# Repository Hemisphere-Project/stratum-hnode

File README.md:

# STRATUM
NodeJS Server / esp8266+W5500 Node

You can find a basic usage in demo.js

### Install
`npm install --save hemisphere-project/stratum-hnode`

### Basic usage
```js
var hnode = require('hnode')();   // load and instanciate the library
var server = new hnode.Server();  // instantiate a server
server.start();                   // start the server
```

### Options
```js
var hnode = require('hnode')({
  // This are the default options
  PORT_SERVER: 3737,            // Working UDP port
  TIME_TICK: 100,               // Watchdog timer ms
  TIME_OFFLINE: 1000,           // Offline Time
  TIME_GONE: 3000,              // Gone Time
  NLEDS_STRIPS: 90,             // N leds per strips
  NSTRIPS_CLIENT: 4,            // N strips per client
  log : msg => console.log(msg) // custom log function (to write in file, etc)
});
var server = new hnode.Server()
server.start()
```

### API
#### Server methods:
  `.getNodeByIP( ip )`      
      return a Node or undefined

  `.getNodeByName( name )`  
       return a Node or undefined

  `.getAllNodes()`  
      return an array with all known Nodes

  `.setAll( rgb )`  
      apply one color (rgb array) to every leds, rgb = [r,g,b]

  `.blackout()`  
      switch off every leds

#### Server events:
  `.on('newnode', function(node){ ... })`   
       triggered when a new Node is discovered

  `.on('tick', function(node){ ... })`
       server ticker, can be use as main sequencer

#### Node methods:
  `.setLed( strip, led, rgb )`   
       apply rgb array to a specific led, rgb = [r, g, b]
       array[3]

  `.setStrip( led, rgbs )`   
       apply rgbs array of array to a strip, rgbs = [ [r, g, b],  [r, g, b], ... ]
       array[NUM_LEDS_PER_STRIP][3]

  `.setAll( rgbs )`   
       apply a whole set of 4 strips, rgbs = [ [ [r, g, b],  [r, g, b], ... ], ... ]
       array[NSTRIPS_PER_CLIENTS][NUM_LEDS_PER_STRIP][3]

  `.randomize()`   
       randomize all values of the node's leds

#### Node attributes (read-only):
  `.name`   
  `.ip`

#### Node events:
  `.on('start', function(node){ ... }) `  
       triggered when a node is started

  `.on('online', function(node){ ... })`   
       triggered when a node goes online

  `.on('offline', function(node){ ... }) `  
       triggered when a node goes offline

  `.on('stop', function(node){ ... }) `  
       triggered when a node is stopped

## TODO:
- Server presence broadcast beacon + Arduino auto-catch server IP
- Arduino client MAC address, and derivative name

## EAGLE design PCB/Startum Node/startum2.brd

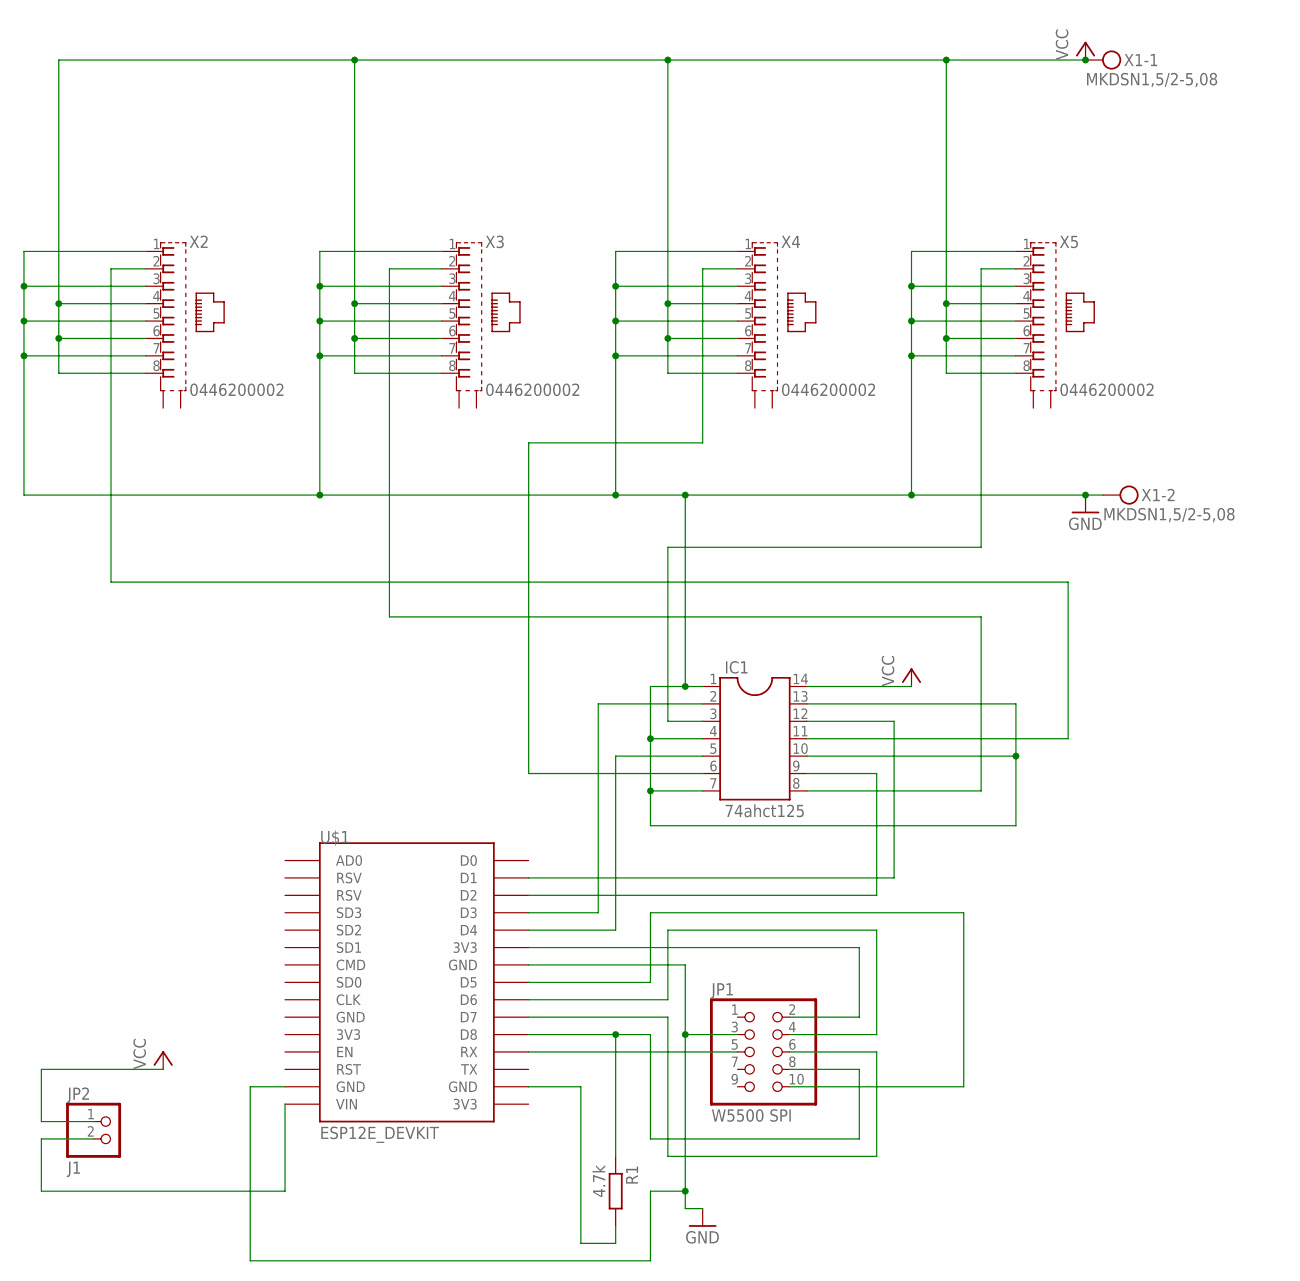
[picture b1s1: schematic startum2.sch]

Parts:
IC1: 74ahct125; DIL14; MPN SN74AHCT125N
JP1: W5500 SPI; 2X05
JP2: J1; 1X02
R1: 4.7k; 0207/10; MPN MCWF08P4701FTL
U$1: ESP12E_DEVKIT
X1: MKDSN1,5/2-5,08
X2, X3, X4, X5: 0446200002

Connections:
GND: IC1.1, IC1.4, IC1.7, IC1.10, IC1.13, JP1.3, U$1.GND@1 (GND), U$1.GND@2 (GND), X1.2, X2.1, X2.3, X2.5, X2.7, X3.1, X3.3, X3.5, X3.7, X4.1, X4.3, X4.5, X4.7, X5.1, X5.3, X5.5, X5.7
unnamed: JP1.2, U$1.3V3@1 (3V3)
unnamed: R1.2, U$1.GND@3 (GND)
unnamed: JP1.10, U$1.D5
unnamed: JP1.4, U$1.D6
unnamed: JP1.6, U$1.D7
unnamed: JP1.8, R1.1, U$1.D8
unnamed: JP1.5, U$1.RX
unnamed: IC1.12, U$1.D1
unnamed: IC1.9, U$1.D2
unnamed: JP2.2, U$1.VIN
unnamed: IC1.6, X4.2
unnamed: IC1.2, U$1.D3
unnamed: IC1.5, U$1.D4
unnamed: IC1.8, X3.2
unnamed: IC1.3, X5.2
unnamed: IC1.11, X2.2
VCC: IC1.14, JP2.1, X1.1, X2.4, X2.6, X2.8, X3.4, X3.6, X3.8, X4.4, X4.6, X4.8, X5.4, X5.6, X5.8

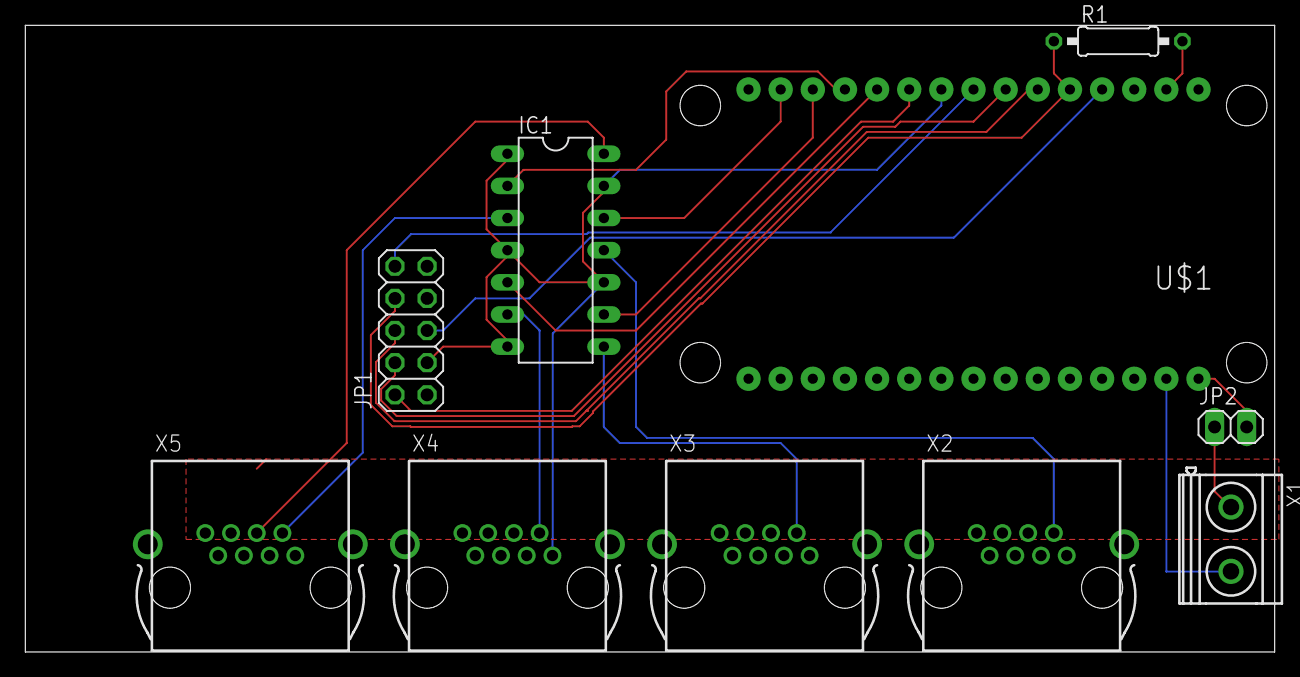
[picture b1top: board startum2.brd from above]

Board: 2 copper layers, 98.7 x 49.5 mm, 10 parts (0 on the bottom side), 18 nets.

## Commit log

2017-09-12 creating socketio and udp benchmarks
2017-09-12 TODO
2017-09-19 mqtt - test
2017-09-19 ETH benchmark
2017-09-19 hnode server module bootstrap
2017-09-19 Base module HServer
2017-09-20 HNode server base version - handling client states
2017-09-24 Refactoring using JS Class
2017-09-28 Refactor as a module + demo app
2017-09-29 Add server methods and fix demo.js
2017-09-29 Fix demo.js & typo in hnode
2017-10-03 change client port to 3738
2017-10-03 Dynmaic client IP & store by name instead of IP
2017-10-03 Fixed wrong calc on led index with multiple strips
2017-10-03 Fixes #1
2017-10-06 Release 0.1.0
2017-10-06 Change module name from stratum-hnode to hnode
2017-10-06 Fix wrong Range error and DRY setLeds methods
    `node.setLed` was returning `undefined` with `key >= NLEDS`, instead of `NLEDS * 3`
2017-10-06 Release 0.1.2
2017-10-06 Fix Server limit & Arduino client: switch to Adafruit Neopixel instead of FastLED
2017-10-09 Add startup sequence for led strip: initial state before connecting
2017-10-09 Updated demo.js with server animation sequencing and FPS
2017-10-09 added TODO list
2017-10-09 Fix Client name, changeable server rate, and fix demo anaimate callback
2017-10-19 Handle server connection lost - Fixes #3
2017-10-27 Fix undefined index in node.setStrip
2017-10-30 Update Hnode2
2017-11-06 arduino4 & arduino5-wifi
2017-11-07 Release 0.1.4
2017-11-15 Remote ctrl KXKM
2017-11-15 KXKM anims
2017-11-21 Arduino Client v6: nodeID to EEPROM
2017-11-23 KXKM sketch
2017-12-01 fix ETH static / MAC
2017-12-17 PCB eagle
2018-01-29 Upgrade to v7 / simplify comm
2018-01-30 0.2.0
2018-10-23 [js] Allow options to be passed at hnode instanciation
2018-10-24 Arduino client v8
2018-10-24 Fix arduino infos out of standard
2018-10-26 test mode
2018-10-26 cleaning master
2018-10-29 remove lockRate // fix empty info bug
2018-10-29 synchronised Dual-buffered refresh to keep udp under 1500 bytes
2018-10-29 Dual Buffer double strip mega trip
2018-10-29 demo and defautlt FPS
2018-11-05 Brightness correction
2018-11-05 version upgrade
2018-11-09 Add option to disable voltage drop correction
    This is useful when using mocked hardware like `rythmus-viewer`
2018-11-09 Release 0.3.2
2019-05-14 fix ethernet lib
2019-05-16 weird fix ethernet2
2020-11-02 demo
